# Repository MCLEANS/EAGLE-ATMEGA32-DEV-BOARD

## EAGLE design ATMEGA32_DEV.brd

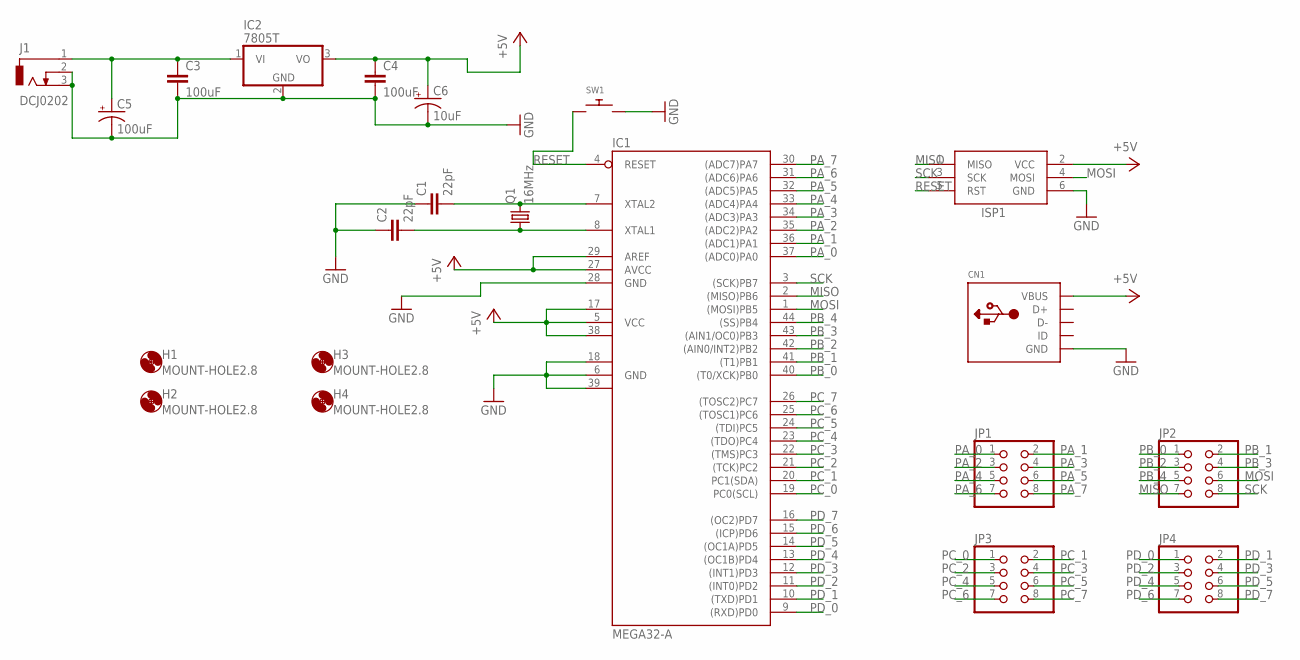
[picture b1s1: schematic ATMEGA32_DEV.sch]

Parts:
C1, C2: 22pF; C0805
C3, C4: 100uF; C0805
C5: 100uF; E5-8,5
C6: 10uF; E5-8,5
CN1: USBMINIB; USB-MINIB
H1, H2, H3, H4: MOUNT-HOLE2.8; 2,8
IC1: MEGA32-A; TQFP44
IC2: 7805T; TO220H
ISP1: AVRISP-BOX
J1: DCJ0202
JP1, JP2, JP3, JP4: PINHD-2X4; 2X04
Q1: 16MHz; HC49/S
SW1: SWITCH_PUSHBUTTONEVQ-PE; TACT_PANA-EVQ

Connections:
+5V: C4.1, C6.+, CN1.VBUS, IC1.5 (VCC), IC1.17 (VCC1), IC1.27 (AVCC), IC1.29 (AREF), IC1.38 (VCC2), IC2.3 (VO), ISP1.2 (VCC)
GND: C1.1, C2.1, C3.2, C4.2, C5.-, C6.-, CN1.GND, IC1.6 (GND), IC1.18 (GND1), IC1.28 (GND), IC1.39 (GND2), IC2.2 (GND), ISP1.6 (GND), J1.2, J1.3, SW1.P$2
MISO: IC1.2 ((MISO)PB6), ISP1.1 (MISO), JP2.7
MOSI: IC1.1 ((MOSI)PB5), ISP1.4 (MOSI), JP2.6
unnamed: C1.2, IC1.7 (XTAL2), Q1.2
unnamed: C2.2, IC1.8 (XTAL1), Q1.1
unnamed: C3.1, C5.+, IC2.1 (VI), J1.1
PA_0: IC1.37 ((ADC0)PA0), JP1.1
PA_1: IC1.36 ((ADC1)PA1), JP1.2
PA_2: IC1.35 ((ADC2)PA2), JP1.3
PA_3: IC1.34 ((ADC3)PA3), JP1.4
PA_4: IC1.33 ((ADC4)PA4), JP1.5
PA_5: IC1.32 ((ADC5)PA5), JP1.6
PA_6: IC1.31 ((ADC6)PA6), JP1.7
PA_7: IC1.30 ((ADC7)PA7), JP1.8
PB_0: IC1.40 ((T0/XCK)PB0), JP2.1
PB_1: IC1.41 ((T1)PB1), JP2.2
PB_2: IC1.42 ((AIN0/INT2)PB2), JP2.3
PB_3: IC1.43 ((AIN1/OC0)PB3), JP2.4
PB_4: IC1.44 ((SS)PB4), JP2.5
PC_0: IC1.19 (PC0(SCL)), JP3.1
PC_1: IC1.20 (PC1(SDA)), JP3.2
PC_2: IC1.21 ((TCK)PC2), JP3.3
PC_3: IC1.22 ((TMS)PC3), JP3.4
PC_4: IC1.23 ((TDO)PC4), JP3.5
PC_5: IC1.24 ((TDI)PC5), JP3.6
PC_6: IC1.25 ((TOSC1)PC6), JP3.7
PC_7: IC1.26 ((TOSC2)PC7), JP3.8
PD_0: IC1.9 ((RXD)PD0), JP4.1
PD_1: IC1.10 ((TXD)PD1), JP4.2
PD_2: IC1.11 ((INT0)PD2), JP4.3
PD_3: IC1.12 ((INT1)PD3), JP4.4
PD_4: IC1.13 ((OC1B)PD4), JP4.5
PD_5: IC1.14 ((OC1A)PD5), JP4.6
PD_6: IC1.15 ((ICP)PD6), JP4.7
PD_7: IC1.16 ((OC2)PD7), JP4.8
RESET: IC1.4 (RESET), ISP1.5 (RST), SW1.P$1
SCK: IC1.3 ((SCK)PB7), ISP1.3 (SCK), JP2.8

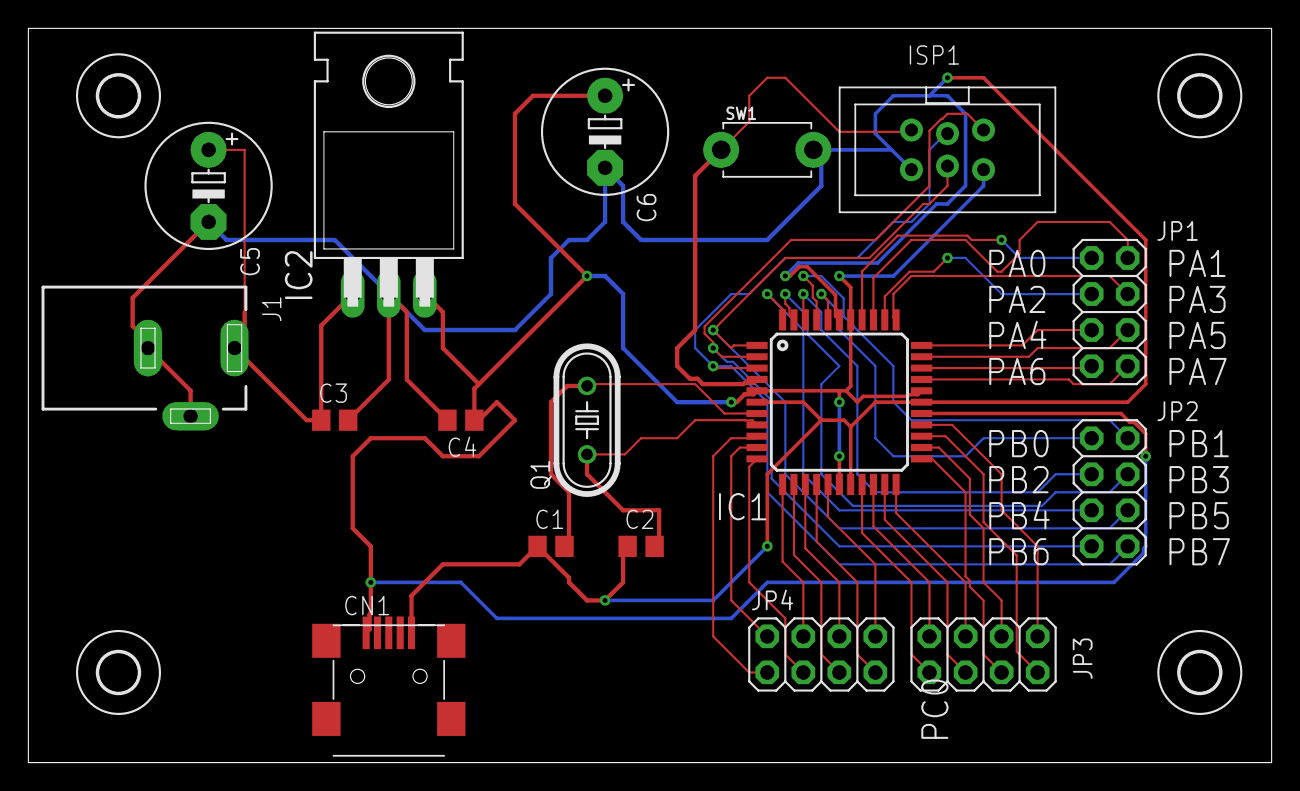
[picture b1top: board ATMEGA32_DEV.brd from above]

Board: 2 copper layers, 87.6 x 51.7 mm, 21 parts (0 on the bottom side), 38 nets.

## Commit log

2020-03-16 development board scematic file
2020-03-16 development board layout
2020-03-16 routed design
2020-03-24 Board Image file
2020-03-24 Included mounting holes
2020-03-24 re_adjusted layout
2020-03-24 removed versions
